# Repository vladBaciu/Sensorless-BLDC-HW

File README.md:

# Bachelor thesis project

## Video: [youtube demonstration for starting](https://www.youtube.com/watch?v=OzBrSzkHfI8&ab_channel=Ataraxy)

## Sensorless BLDC Controller using BEMF and Zero Crossing Point (ZCP) Detection

## Software: https://github.com/vladBaciu/Sensorless-BLDC-CODE

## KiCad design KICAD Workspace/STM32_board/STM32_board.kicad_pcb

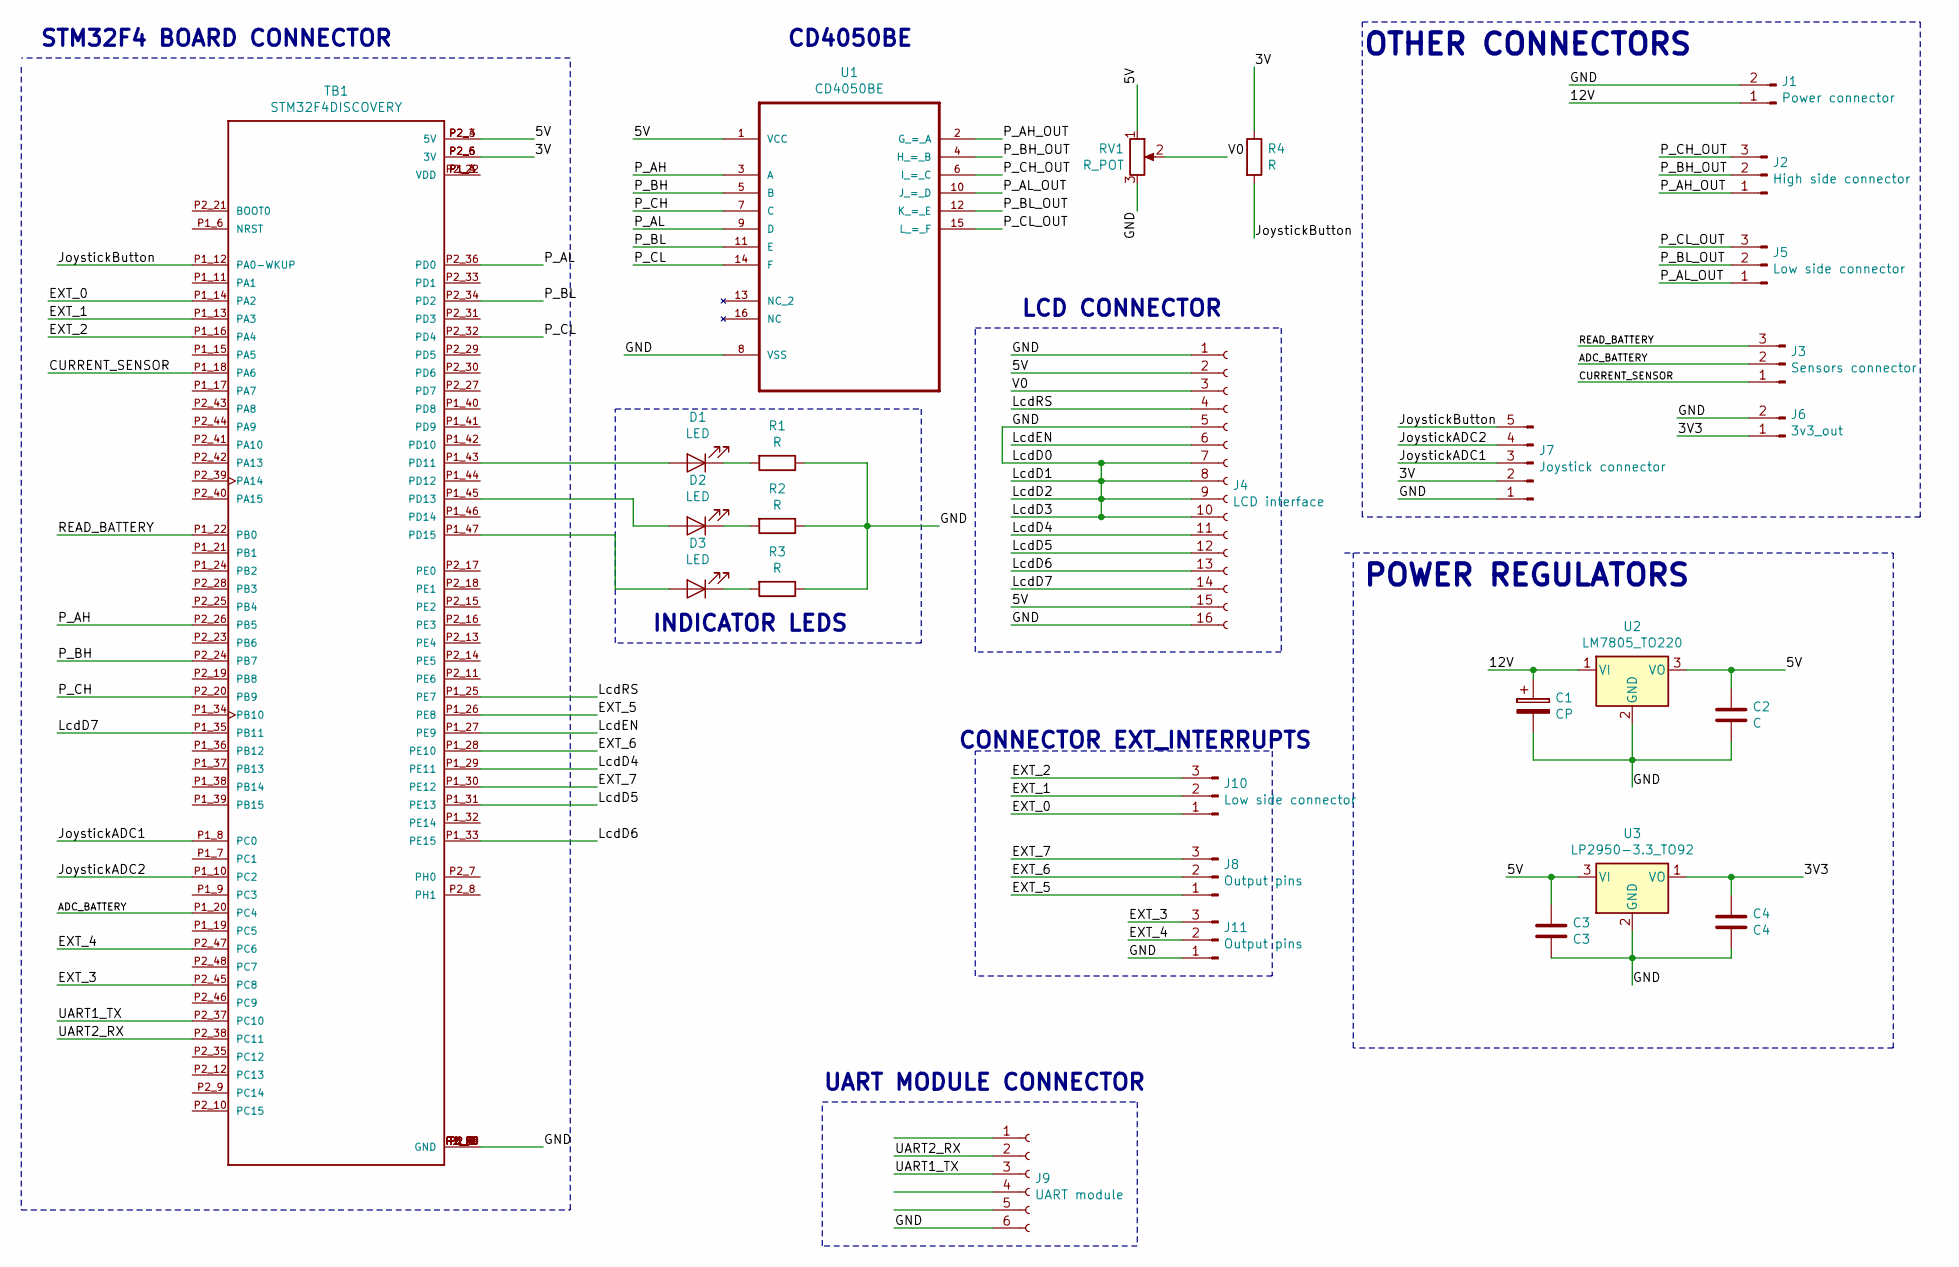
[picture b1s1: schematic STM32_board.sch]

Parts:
C1: CP; CP_Radial_D8.0mm_P3.50mm
C2: C; CP_Radial_D8.0mm_P3.50mm
C3: C3; CP_Radial_D8.0mm_P3.50mm
C4: C4; CP_Radial_D8.0mm_P3.50mm
D1, D2, D3: LED; LED_D5.0mm
J1: Power connector; PhoenixContact_MSTBA_2,5_2-G-5,08_1x02_P5.08mm_Horizontal
J2: High side connector; PinSocket_1x03_P2.54mm_Vertical
J3: Sensors connector; PinSocket_1x03_P2.54mm_Vertical
J4: LCD interface; PinSocket_1x16_P2.54mm_Vertical
J5, J10: Low side connector; PinSocket_1x03_P2.54mm_Vertical
J6: 3v3_out; PinSocket_1x02_P2.54mm_Vertical
J7: Joystick connector; PinSocket_1x05_P2.54mm_Vertical
J8, J11: Output pins; PinSocket_1x03_P2.54mm_Vertical
J9: UART module; PinHeader_1x06_P2.54mm_Vertical
R1, R2, R3, R4: R; R_Axial_DIN0411_L9.9mm_D3.6mm_P15.24mm_Horizontal
RV1: R_POT; Potentiometer_Alps_RK163_Single_Horizontal
TB1: STM32F4DISCOVERY; MODULE_STM32F4DISCOVERY
U1: CD4050BE; DIP254P762X508-16
U2: LM7805_TO220; TO-220-3_Vertical
U3: LP2950-3.3_TO92; TO-92_Inline

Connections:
/3V: J7.2, R4.1, TB1.P2_5 (3V), TB1.P2_6 (3V)
/3V3: C4.1, J6.1, U3.1 (VO)
/5V: C2.1, C3.1, J4.2, J4.15, RV1.1, TB1.P2_3 (5V), TB1.P2_4 (5V), U1.1 (VCC), U2.3 (VO), U3.3 (VI)
/12V: C1.1, J1.1, U2.1 (VI)
/ADC_BATTERY: J3.2, TB1.P1_20 (PC4)
/CURRENT_SENSOR: J3.1, TB1.P1_18 (PA6)
/EXT_0: J10.1, TB1.P1_14 (PA2)
/EXT_1: J10.2, TB1.P1_13 (PA3)
/EXT_2: J10.3, TB1.P1_16 (PA4)
/EXT_3: J11.3, TB1.P2_45 (PC8)
/EXT_4: J11.2, TB1.P2_47 (PC6)
/EXT_5: J8.1, TB1.P1_26 (PE8)
/EXT_6: J8.2, TB1.P1_28 (PE10)
/EXT_7: J8.3, TB1.P1_30 (PE12)
/GND: C1.2, C2.2, C3.2, C4.2, J1.2, J4.1, J4.5, J4.7, J4.8, J4.9, J4.10, J4.16, J6.2, J7.1, J9.6, J11.1, R1.1, R2.1, R3.1, RV1.3, TB1.P1_1 (GND), TB1.P1_2 (GND), TB1.P1_5 (GND), TB1.P1_23 (GND), TB1.P1_49 (GND), TB1.P1_50 (GND), TB1.P2_1 (GND), TB1.P2_2 (GND), TB1.P2_49 (GND), TB1.P2_50 (GND), U1.8 (VSS), U2.2 (GND), U3.2 (GND)
/JoystickADC1: J7.3, TB1.P1_8 (PC0)
/JoystickADC2: J7.4, TB1.P1_10 (PC2)
/JoystickButton: J7.5, R4.2, TB1.P1_12 (PA0-WKUP)
/LcdD4: J4.11, TB1.P1_29 (PE11)
/LcdD5: J4.12, TB1.P1_31 (PE13)
/LcdD6: J4.13, TB1.P1_33 (PE15)
/LcdD7: J4.14, TB1.P1_35 (PB11)
/LcdEN: J4.6, TB1.P1_27 (PE9)
/LcdRS: J4.4, TB1.P1_25 (PE7)
/P_AH: TB1.P2_26 (PB5), U1.3 (A)
/P_AH_OUT: J2.1, U1.2 (G_=_A)
/P_AL: TB1.P2_36 (PD0), U1.9 (D)
/P_AL_OUT: J5.1, U1.10 (J_=_D)
/P_BH: TB1.P2_24 (PB7), U1.5 (B)
/P_BH_OUT: J2.2, U1.4 (H_=_B)
/P_BL: TB1.P2_34 (PD2), U1.11 (E)
/P_BL_OUT: J5.2, U1.12 (K_=_E)
/P_CH: TB1.P2_20 (PB9), U1.7 (C)
/P_CH_OUT: J2.3, U1.6 (I_=_C)
/P_CL: TB1.P2_32 (PD4), U1.14 (F)
/P_CL_OUT: J5.3, U1.15 (L_=_F)
/READ_BATTERY: J3.3, TB1.P1_22 (PB0)
/UART1_TX: J9.3, TB1.P2_37 (PC10)
/UART2_RX: J9.2, TB1.P2_38 (PC11)
/V0: J4.3, RV1.2
unnamed: D1.1 (K), R1.2
unnamed: D1.2 (A), TB1.P1_43 (PD11)
unnamed: D2.1 (K), R2.2
unnamed: D2.2 (A), TB1.P1_45 (PD13)
unnamed: D3.1 (K), R3.2
unnamed: D3.2 (A), TB1.P1_47 (PD15)
unnamed: TB1.P1_3 (VDD), TB1.P1_4 (VDD), TB1.P2_22 (VDD)

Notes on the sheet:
POWER REGULATORS
OTHER CONNECTORS
UART MODULE CONNECTOR
CONNECTOR EXT_INTERRUPTS
LCD CONNECTOR
STM32F4 BOARD CONNECTOR
CD4050BE
INDICATOR LEDS

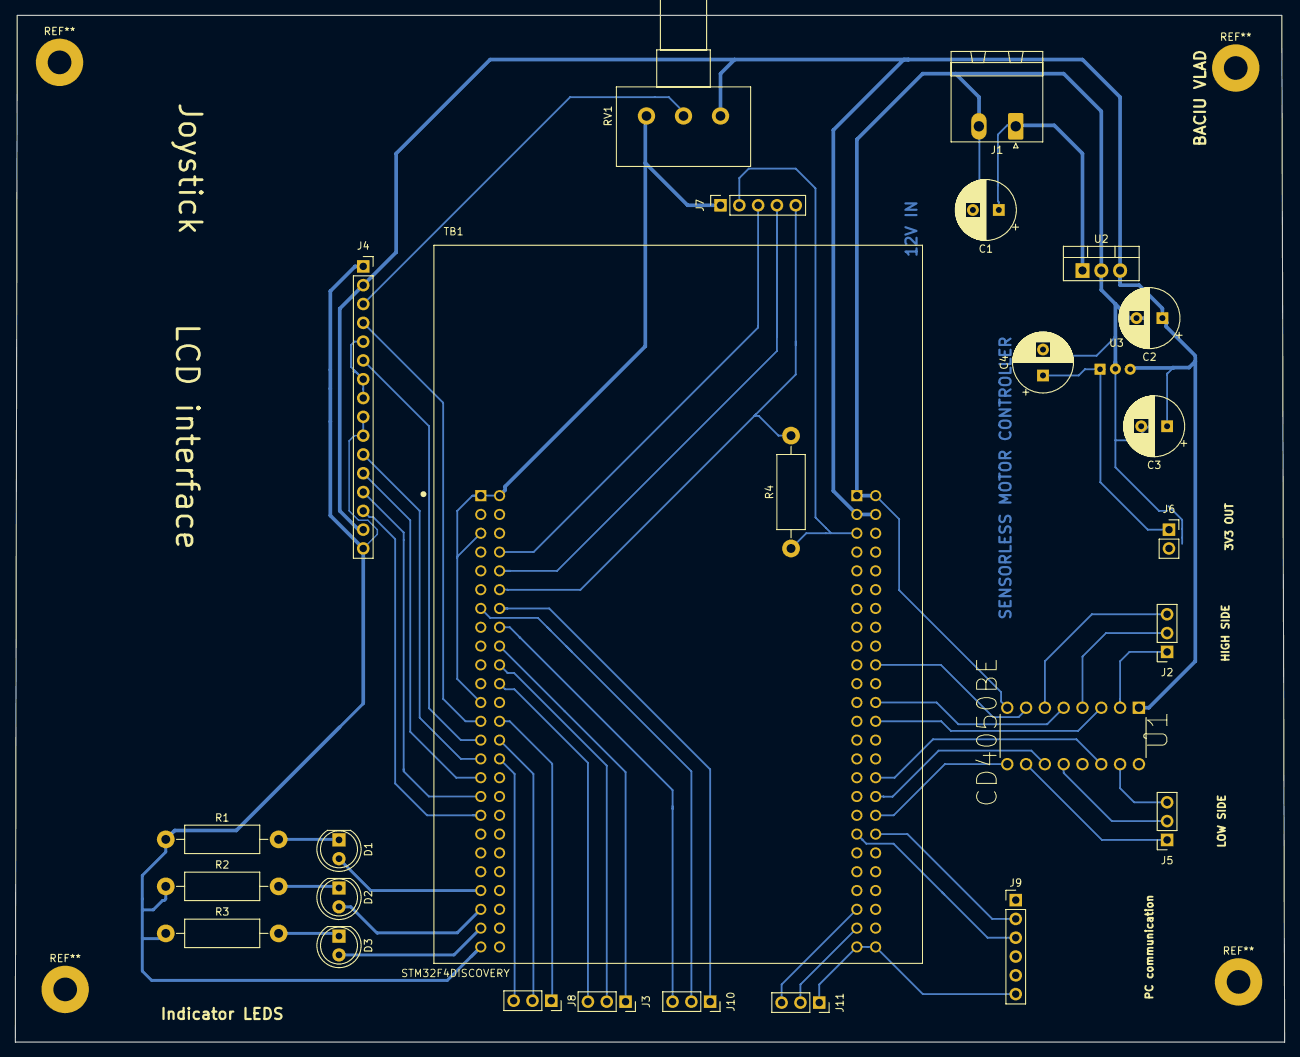
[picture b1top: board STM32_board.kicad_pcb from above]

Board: 2 copper layers, 171.4 x 138.7 mm, 27 parts (0 on the bottom side), 47 nets.

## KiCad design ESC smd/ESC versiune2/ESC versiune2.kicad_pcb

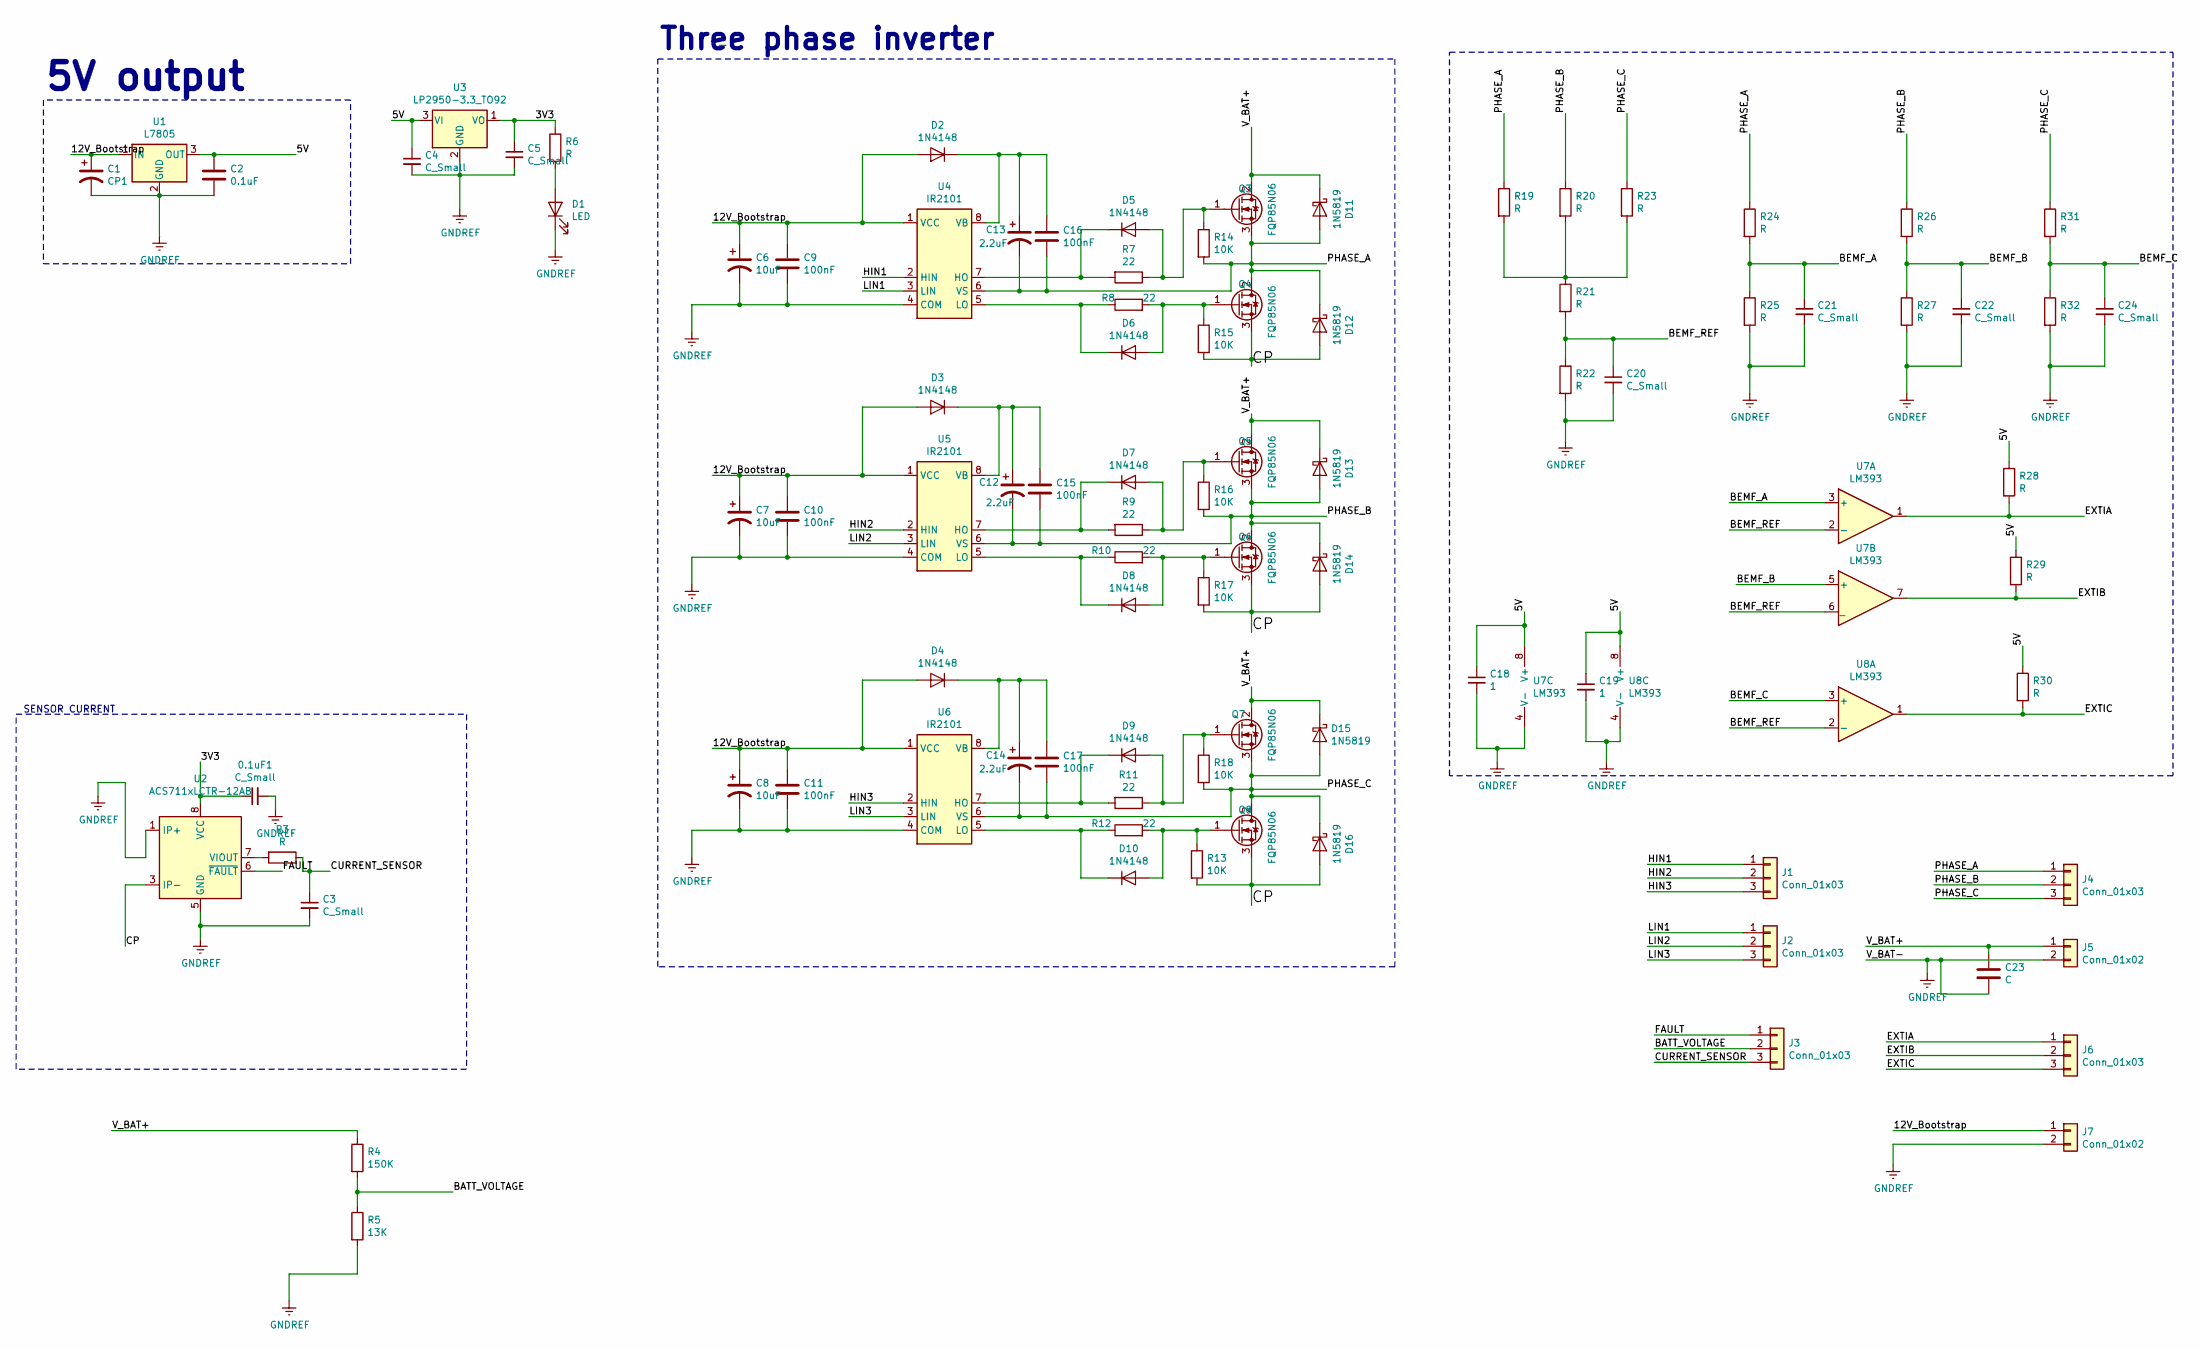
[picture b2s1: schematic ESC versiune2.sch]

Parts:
0.1uF1: C_Small; C_1206_3216Metric_Pad1.42x1.75mm_HandSolder
C1: CP1; C_Elec_5x5.4
C2: 0.1uF; C_1206_3216Metric_Pad1.42x1.75mm_HandSolder
C3, C4, C5, C20, C21, C22, C24: C_Small; C_1206_3216Metric_Pad1.42x1.75mm_HandSolder
C6, C7, C8: 10uF; C_Elec_5x5.4
C9, C10, C11, C15, C16, C17: 100nF; C_1206_3216Metric_Pad1.42x1.75mm_HandSolder
C12, C13, C14: 2.2uF; C_1206_3216Metric_Pad1.42x1.75mm_HandSolder
C18, C19: 1; C_1206_3216Metric_Pad1.42x1.75mm_HandSolder
C23: C; CP_Radial_D18.0mm_P7.50mm
D1: LED; LED_1206_3216Metric_Pad1.42x1.75mm_HandSolder
D2, D3, D4, D5, D6, D7, D8, D9, D10: 1N4148; D_1206_3216Metric_Pad1.42x1.75mm_HandSolder
D11, D12, D13, D14, D15, D16: 1N5819; D_SOD-123F
J1, J2, J3, J6: Conn_01x03; PinHeader_1x03_P2.54mm_Vertical
J4: Conn_01x03; MOTOR_CONNECTOR
J5: Conn_01x02; PhoenixContact_MSTBVA_2,5_2-G-5,08_1x02_P5.08mm_Vertical
J7: Conn_01x02; PinHeader_1x02_P2.54mm_Vertical
Q3, Q4, Q5, Q6, Q7, Q8: FQP85N06; TO-252-2
R3, R6, R19, R20, R21, R22, R23, R24, R25, R26, R27, R28, R29, R30, R31, R32: R; R_1206_3216Metric_Pad1.42x1.75mm_HandSolder
R4: 150K; R_1206_3216Metric_Pad1.42x1.75mm_HandSolder
R5: 13K; R_1206_3216Metric_Pad1.42x1.75mm_HandSolder
R7, R8, R9, R10, R11, R12: 22; R_2512_6332Metric_Pad1.52x3.35mm_HandSolder
R13, R14, R15, R16, R17, R18: 10K; R_1206_3216Metric_Pad1.42x1.75mm_HandSolder
U1: L7805; TO-263-2
U2: ACS711xLCTR-12AB; SOIC-8_3.9x4.9mm_P1.27mm
U3: LP2950-3.3_TO92; SOT-223-3_TabPin2_Modificat
U4, U5, U6: IR2101; SOIC127P490X600X175-8N
U7, U8: LM393; SOIC127P600X175-8N

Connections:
/3V3: 0.1uF1.1, C5.1, R6.1, U2.8 (VCC), U3.1 (VO); also elsewhere on the board
/5V: C2.1, C4.1, C18.1, C19.1, R28.1, R29.1, R30.1, U1.3 (OUT), U3.3 (VI), U7.8 (V+), U8.8 (V+)
/12V_Bootstrap: C1.1, C6.1, C7.1, C8.1, C9.1, C10.1, C11.1, D2.2 (A), D3.2 (A), D4.2 (A), J7.1, U1.1 (IN), U4.1 (VCC), U5.1 (VCC), U6.1 (VCC)
/BATT_VOLTAGE: J3.2, R4.2, R5.1
/BEMF_A: C21.1, R24.2, R25.1, U7.3 (+)
/BEMF_B: C22.1, R26.2, R27.1, U7.5 (+)
/BEMF_C: C24.1, R31.2, R32.1, U8.3 (+)
/BEMF_REF: C20.1, R21.2, R22.1, U7.2 (-), U7.6 (_), U8.2 (-)
/CP: D12.2 (A), D14.2 (A), D16.2 (A), Q4.3 (S), Q6.3 (S), Q8.3 (S), R13.2, R15.2, R17.2, U2.3 (IP-), U2.4 (IP-)
/CURRENT_SENSOR: C3.1, J3.3, R3.1
/EXTIA: J6.1, R28.2, U7.1
/EXTIB: J6.2, R29.2, U7.7
/EXTIC: J6.3, R30.2, U8.1
/FAULT: J3.1, U2.6 (~FAULT)
/HIN1: J1.1, U4.2 (HIN)
/HIN2: J1.2, U5.2 (HIN)
/HIN3: J1.3, U6.2 (HIN)
/LIN1: J2.1, U4.3 (LIN)
/LIN2: J2.2, U5.3 (LIN)
/LIN3: J2.3, U6.3 (LIN)
/PHASE_A: C13.2, C16.2, D11.2 (A), D12.1 (K), J4.1, Q3.3 (S), Q4.2 (D), R14.2, R19.1, R24.1, U4.6 (VS)
/PHASE_B: C12.2, C15.2, D13.2 (A), D14.1 (K), J4.2, Q5.3 (S), Q6.2 (D), R16.2, R20.1, R26.1, U5.6 (VS)
/PHASE_C: C14.2, C17.2, D15.2 (A), D16.1 (K), J4.3, Q7.3 (S), Q8.2 (D), R18.2, R23.1, R31.1, U6.6 (VS)
/V_BAT+: C23.1, D11.1 (K), D13.1 (K), D15.1 (K), J5.1, Q3.2 (D), Q5.2 (D), Q7.2 (D), R4.1
GNDREF: 0.1uF1.2, C1.2, C2.2, C3.2, C4.2, C5.2, C6.2, C7.2, C8.2, C9.2, C10.2, C11.2, C18.2, C19.2, C20.2, C21.2, C22.2, C23.2, C24.2, D1.1 (K), J5.2, J7.2, R5.2, R22.2, R25.2, R27.2, R32.2, U1.2 (GND), U2.1 (IP+), U2.2 (IP+), U2.5 (GND), U3.2 (GND), U4.4 (COM), U5.4 (COM), U6.4 (COM), U7.4 (V-), U8.4 (V-); also elsewhere on the board
unnamed: C12.1, C15.1, D3.1 (K), U5.8 (VB)
unnamed: C13.1, C16.1, D2.1 (K), U4.8 (VB)
unnamed: C14.1, C17.1, D4.1 (K), U6.8 (VB)
unnamed: D1.2 (A), R6.2
unnamed: D5.1 (K), R7.2, U4.7 (HO)
unnamed: D5.2 (A), Q3.1 (G), R7.1, R14.1
unnamed: D6.1 (K), R8.1, U4.5 (LO)
unnamed: D6.2 (A), Q4.1 (G), R8.2, R15.1
unnamed: D7.1 (K), R9.2, U5.7 (HO)
unnamed: D7.2 (A), Q5.1 (G), R9.1, R16.1
unnamed: D8.1 (K), R10.1, U5.5 (LO)
unnamed: D8.2 (A), Q6.1 (G), R10.2, R17.1
unnamed: D9.1 (K), R11.2, U6.7 (HO)
unnamed: D9.2 (A), Q7.1 (G), R11.1, R18.1
unnamed: D10.1 (K), R12.1, U6.5 (LO)
unnamed: D10.2 (A), Q8.1 (G), R12.2, R13.1
unnamed: R3.2, U2.7 (VIOUT)
unnamed: R19.2, R20.2, R21.1, R23.2

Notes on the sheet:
SENSOR CURRENT
5V output
Three phase inverter

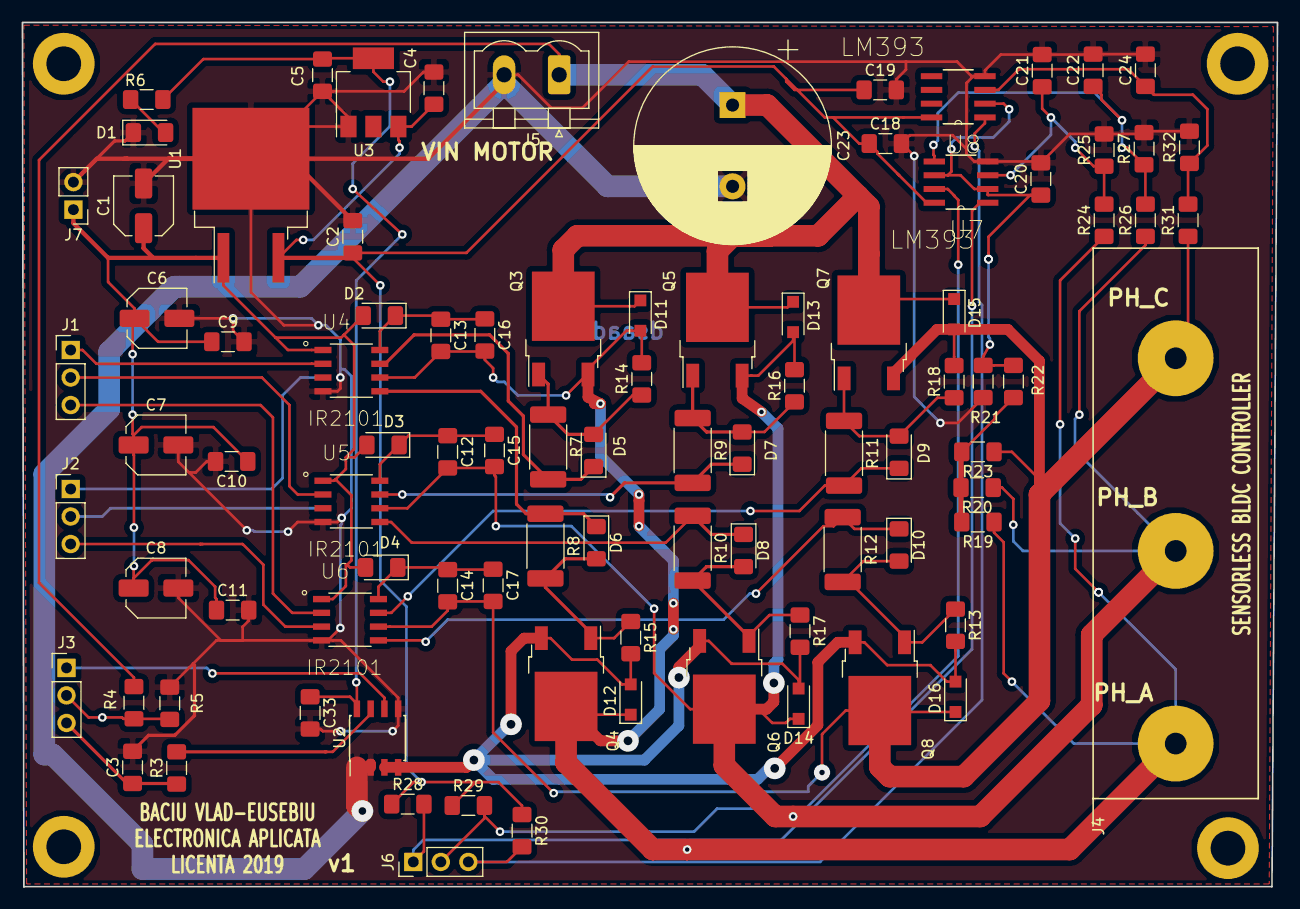
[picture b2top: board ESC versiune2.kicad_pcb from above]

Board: 2 copper layers, 115.8 x 79.8 mm, 92 parts (0 on the bottom side), 43 nets.

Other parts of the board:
C33: C_Small; C_1206_3216Metric_Pad1.42x1.75mm_HandSolder

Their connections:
/3V3: C33.1; also elsewhere on the board
GNDREF: C33.2; also elsewhere on the board

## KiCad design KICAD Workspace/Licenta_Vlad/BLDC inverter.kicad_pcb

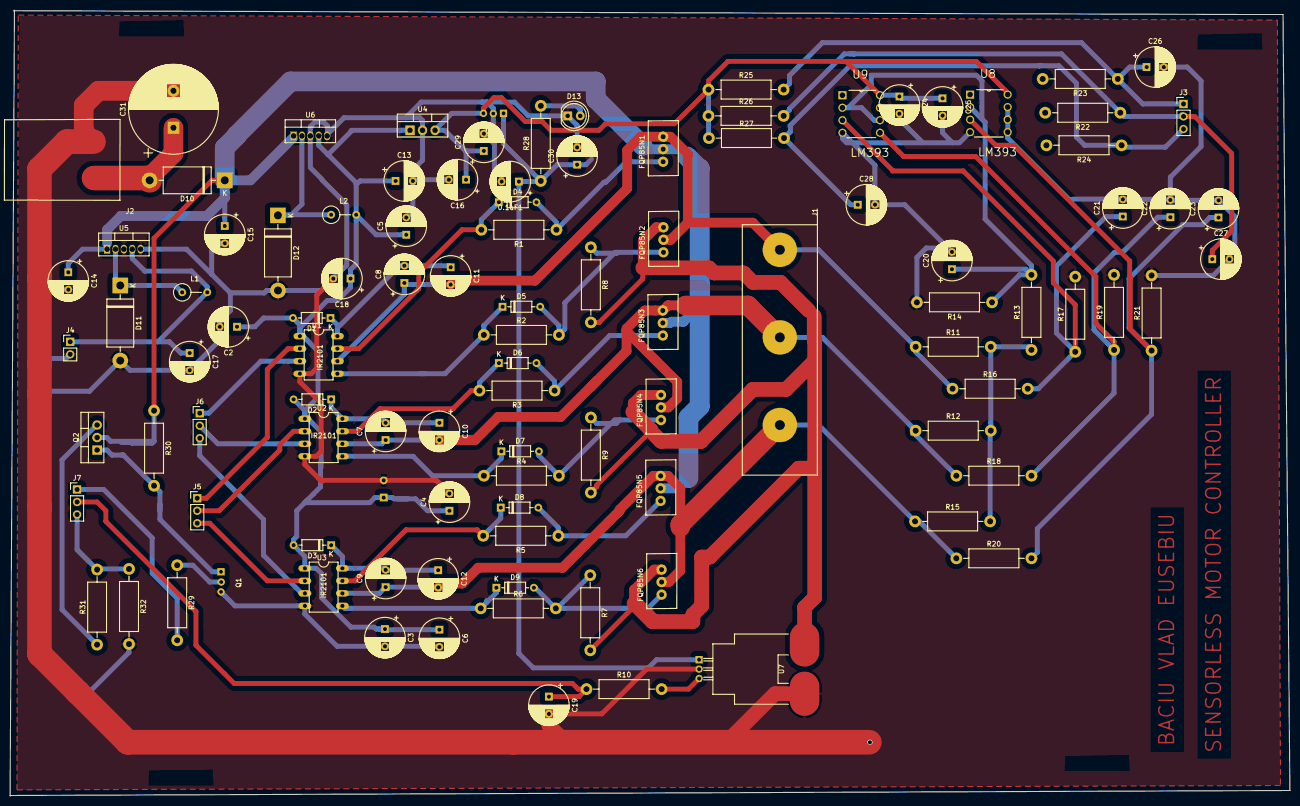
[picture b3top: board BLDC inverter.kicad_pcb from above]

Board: 2 copper layers, 259.7 x 159.5 mm, 104 parts (1 on the bottom side), 53 nets.

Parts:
0.1uF1: C_Small; CP_Radial_D8.0mm_P3.50mm
C1, C2, C3, C7, C8, C9: 10uF; CP_Radial_D8.0mm_P3.50mm
C4, C5, C6, C10, C11, C12: 100nF; CP_Radial_D8.0mm_P3.50mm
C13: CP1; CP_Radial_D8.0mm_P3.50mm
C14, C15: 100uF; CP_Radial_D8.0mm_P3.50mm
C16: 0.1uF; CP_Radial_D8.0mm_P3.50mm
C17, C18: 330uF; CP_Radial_D8.0mm_P3.50mm
C19, C20, C21, C22, C23, C26, C27, C28, C29, C30: C_Small; CP_Radial_D8.0mm_P3.50mm
C24, C25: 1; CP_Radial_D8.0mm_P3.50mm
C31: C; CP_Radial_D18.0mm_P7.50mm
D1, D2, D3, D4, D5, D6, D7, D8, D9: 1N4148; D_DO-35_SOD27_P7.62mm_Horizontal
D10: 1N5061; D_DO-201AD_P15.24mm_Horizontal
D11, D12: 1N5828; D_DO-201AD_P15.24mm_Horizontal
D13: LED; LED_D5.0mm
FQP85N1, FQP85N2, FQP85N3, FQP85N4, FQP85N5, FQP85N6: Q_NMOS_DGS; FQP85N06
J1: Conn_01x03; MOTOR_CONNECTOR
J2: Conn_01x02; XT60
J3, J5, J6, J7: Conn_01x03; PinHeader_1x03_P2.54mm_Vertical
J4: Conn_01x02; PinHeader_1x02_P2.54mm_Vertical
L1, L2: 300uH; L_Axial_L7.0mm_D3.3mm_P5.08mm_Vertical_Fastron_MICC
Q1: BC547; TO-92_Inline
Q2: IRF9530; TO-220-3_Vertical
R1, R2, R3, R4, R5, R6: 22; R_Axial_DIN0411_L9.9mm_D3.6mm_P15.24mm_Horizontal
R7, R8, R9: 150k; R_Axial_DIN0411_L9.9mm_D3.6mm_P15.24mm_Horizontal
R10, R11, R12, R13, R14, R15, R16, R17, R18, R19, R20, R21, R22, R23, R24, R25, R26, R27, R28: R; R_Axial_DIN0411_L9.9mm_D3.6mm_P15.24mm_Horizontal
R29, R30: 10K; R_Axial_DIN0411_L9.9mm_D3.6mm_P15.24mm_Horizontal
R31: 150K; R_Axial_DIN0411_L9.9mm_D3.6mm_P15.24mm_Horizontal
R32: 13K; R_Axial_DIN0411_L9.9mm_D3.6mm_P15.24mm_Horizontal
U1, U2, U3: IR2101; DIL08
U4: L7805; TO-220-3_Vertical
U5, U6: LM2576HVT-12; TO-220-5_Vertical
U7: ACS754; Allegro_CB_PFF
U8, U9: LM393; DIP254P762X508-8
U10: LP2950-3.3_TO92; TO-92_Inline

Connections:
/Sheet5CB00087/3V3: 0.1uF1.1, C30.1, R28.1, U7.1, U10.1
/Sheet5CB00087/5V: C16.1, C24.1, C25.1, C29.1, R25.1, R26.1, R27.1, U4.3, U8.8, U9.8, U10.3
/Sheet5CB00087/12V_Board: C17.1, J4.1, L1.2, U5.4
/Sheet5CB00087/12V_Bootstrap: C1.1, C2.1, C3.1, C4.1, C5.1, C6.1, C13.1, C18.1, D1.2, D2.2, D3.2, L2.2, U1.1, U2.1, U3.1, U4.1, U6.4
/Sheet5CB00087/BATT_VOLTAGE: J7.3, R31.2, R32.1
/Sheet5CB00087/BEMF_A: C21.1, R16.2, R17.1, U9.3
/Sheet5CB00087/BEMF_B: C22.1, R18.2, R19.1, U9.5
/Sheet5CB00087/BEMF_C: C23.1, R20.2, R21.1, U8.3
/Sheet5CB00087/BEMF_REF: C20.1, R13.2, R14.1, U8.2, U9.2, U9.6
/Sheet5CB00087/CP: FQP85N2.3, FQP85N4.3, FQP85N6.3, R7.2, R8.2, R9.2, U7.5
/Sheet5CB00087/CURRENT_SENSOR: C19.1, J7.2, R10.1
/Sheet5CB00087/EXTIA: C26.1, J3.1, R23.1, R25.2
/Sheet5CB00087/EXTIB: C27.1, J3.2, R22.1, R26.2
/Sheet5CB00087/EXTIC: C28.1, J3.3, R24.1, R27.2
/Sheet5CB00087/HIN1: J5.1, U1.2
/Sheet5CB00087/HIN2: J5.2, U2.2
/Sheet5CB00087/HIN3: J5.3, U3.2
/Sheet5CB00087/LIN1: J6.1, U1.3
/Sheet5CB00087/LIN2: J6.2, U2.3
/Sheet5CB00087/LIN3: J6.3, U3.3
/Sheet5CB00087/PHASE_A: C8.1, C11.2, FQP85N1.3, FQP85N2.1, J1.1, R11.1, R16.1, U1.6
/Sheet5CB00087/PHASE_B: C7.1, C10.2, FQP85N3.3, FQP85N4.1, J1.2, R12.1, R18.1, U2.6
/Sheet5CB00087/PHASE_C: C9.1, C12.2, FQP85N5.3, FQP85N6.1, J1.3, R15.1, R20.1, U3.6
/Sheet5CB00087/READ_CMD: J7.1, R29.2
/Sheet5CB00087/V_BAT2+: C14.1, C15.1, D10.1, FQP85N1.1, FQP85N3.1, FQP85N5.1, Q2.2, R30.1, U5.1, U6.1
/Sheet5CB00087/V_BAT+: C31.1, D10.2, J2.1
GNDREF: 0.1uF1.2, C1.2, C2.2, C3.2, C4.2, C5.2, C6.2, C13.2, C14.2, C15.2, C16.2, C17.2, C18.2, C19.2, C20.2, C21.2, C22.2, C23.2, C24.2, C25.2, C26.2, C27.2, C28.2, C29.2, C30.2, C31.2, D11.2, D12.2, D13.1, J2.2, J4.2, Q1.3, R14.2, R17.2, R19.2, R21.2, R32.2, U1.4, U2.4, U3.4, U4.2, U5.3, U5.5, U6.3, U6.5, U7.2, U7.4, U8.4, U9.4, U10.2
unnamed: C7.2, C10.1, D2.1, U2.8
unnamed: C8.2, C11.1, D1.1, U1.8
unnamed: C9.2, C12.1, D3.1, U3.8
unnamed: D4.1, R1.2, U1.7
unnamed: D4.2, FQP85N1.2, R1.1
unnamed: D5.1, R2.1, U1.5
unnamed: D5.2, FQP85N2.2, R2.2, R8.1
unnamed: D6.1, R3.2, U2.7
unnamed: D6.2, FQP85N3.2, R3.1
unnamed: D7.1, R4.1, U2.5
unnamed: D7.2, FQP85N4.2, R4.2, R9.1
unnamed: D8.1, R5.2, U3.7
unnamed: D8.2, FQP85N5.2, R5.1
unnamed: D9.1, R6.1, U3.5
unnamed: D9.2, FQP85N6.2, R6.2, R7.1
unnamed: D11.1, L1.1, U5.2
unnamed: D12.1, L2.1, U6.2
unnamed: D13.2, R28.2
unnamed: Q1.1, Q2.1, R30.2
unnamed: Q1.2, R29.1
unnamed: Q2.3, R31.1
unnamed: R10.2, U7.3
unnamed: R11.2, R12.2, R13.1, R15.2
unnamed: R22.2, U9.7
unnamed: R23.2, U9.1
unnamed: R24.2, U8.1

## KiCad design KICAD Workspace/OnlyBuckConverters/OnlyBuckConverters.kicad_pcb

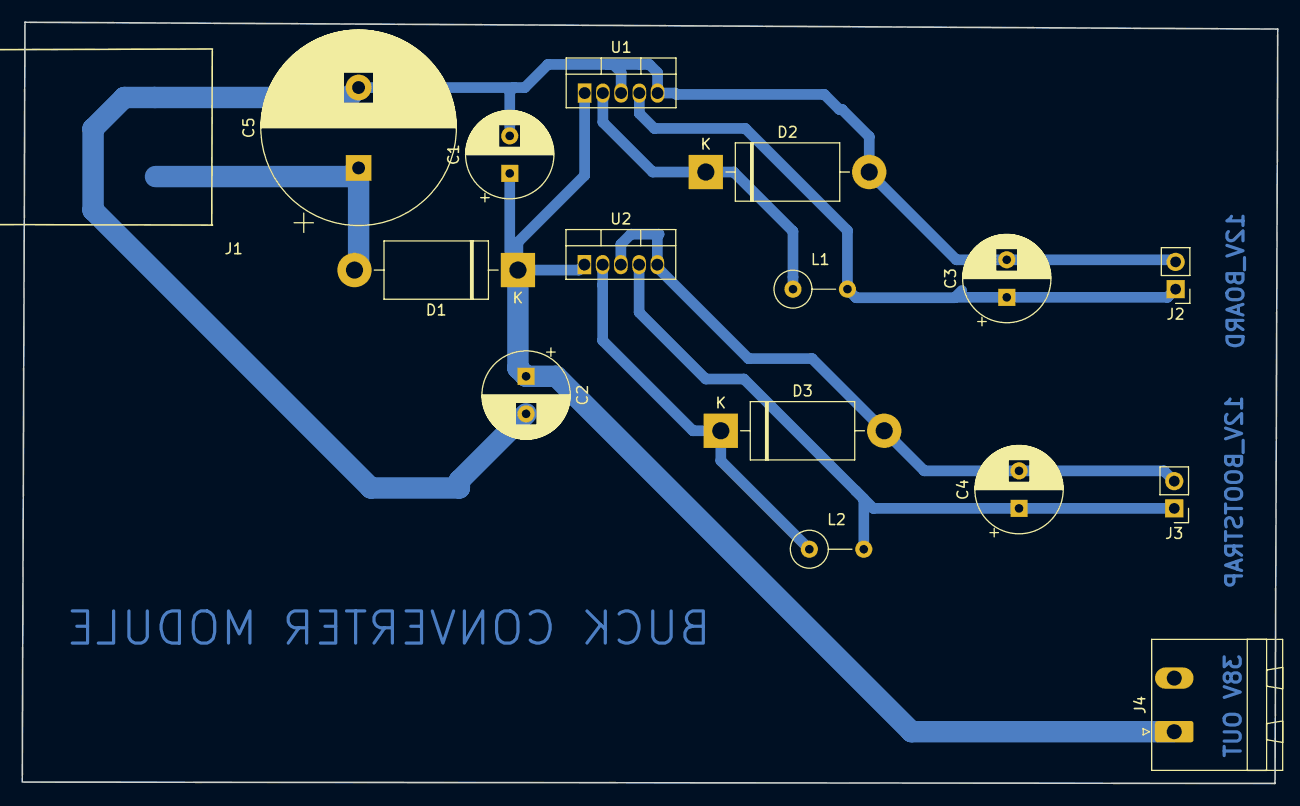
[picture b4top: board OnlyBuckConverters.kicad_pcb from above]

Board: 2 copper layers, 117.1 x 71.0 mm, 16 parts (0 on the bottom side), 7 nets.

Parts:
C1, C2: 100uF; CP_Radial_D8.0mm_P3.50mm
C3, C4: 330uF; CP_Radial_D8.0mm_P3.50mm
C5: C; CP_Radial_D18.0mm_P7.50mm
D1: 1N5061; D_DO-201AD_P15.24mm_Horizontal
D2, D3: 1N5828; D_DO-201AD_P15.24mm_Horizontal
J1: Conn_01x02; XT60
J2, J3: Conn_01x02; PinHeader_1x02_P2.54mm_Vertical
J4: Conn_01x02; PhoenixContact_MSTBA_2,5_2-G_1x02_P5.00mm_Horizontal
L1, L2: 300uH; L_Axial_L7.0mm_D3.3mm_P5.08mm_Vertical_Fastron_MICC
U1, U2: LM2576HVT-12; TO-220-5_Vertical

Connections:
/12V_Board: C3.1, J2.1, L1.2, U1.4
/12V_Bootstrap: C4.1, J3.1, L2.2, U2.4
/V_BAT2+: C1.1, C2.1, D1.1, J4.1, U1.1, U2.1
/V_BAT+: C5.1, D1.2, J1.1
GNDREF: C1.2, C2.2, C3.2, C4.2, C5.2, D2.2, D3.2, J1.2, J2.2, J3.2, J4.2, U1.3, U1.5, U2.3, U2.5
unnamed: D2.1, L1.1, U1.2
unnamed: D3.1, L2.1, U2.2

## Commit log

2019-03-05 First push. Stage: Main board pcb in progress.
2019-03-05 Added picture with pin configuration
2019-03-05 Added some footprints and conenctors
2019-03-06 Added some footprints.
2019-03-12 Added modified PCB
2019-03-12 Modifications of layout. Added some connectors, deleted others, pins connections changed
2019-03-12 Added some modifications to UART connector.
2019-03-17 Final version for printing (i hope)
2019-03-22 Added schematic for BEMF.
2019-03-28 Added some footprints and some traces in PCB editor
2019-03-29 PCB version 1 after big big failure .......................
2019-03-31 Added inverter (only) pcb.
2019-05-12 Added SMD version of ESC.
2019-05-19 Added 3d model for boostrap capacitor
2019-06-13 SMD version
2020-04-09 Add step file
